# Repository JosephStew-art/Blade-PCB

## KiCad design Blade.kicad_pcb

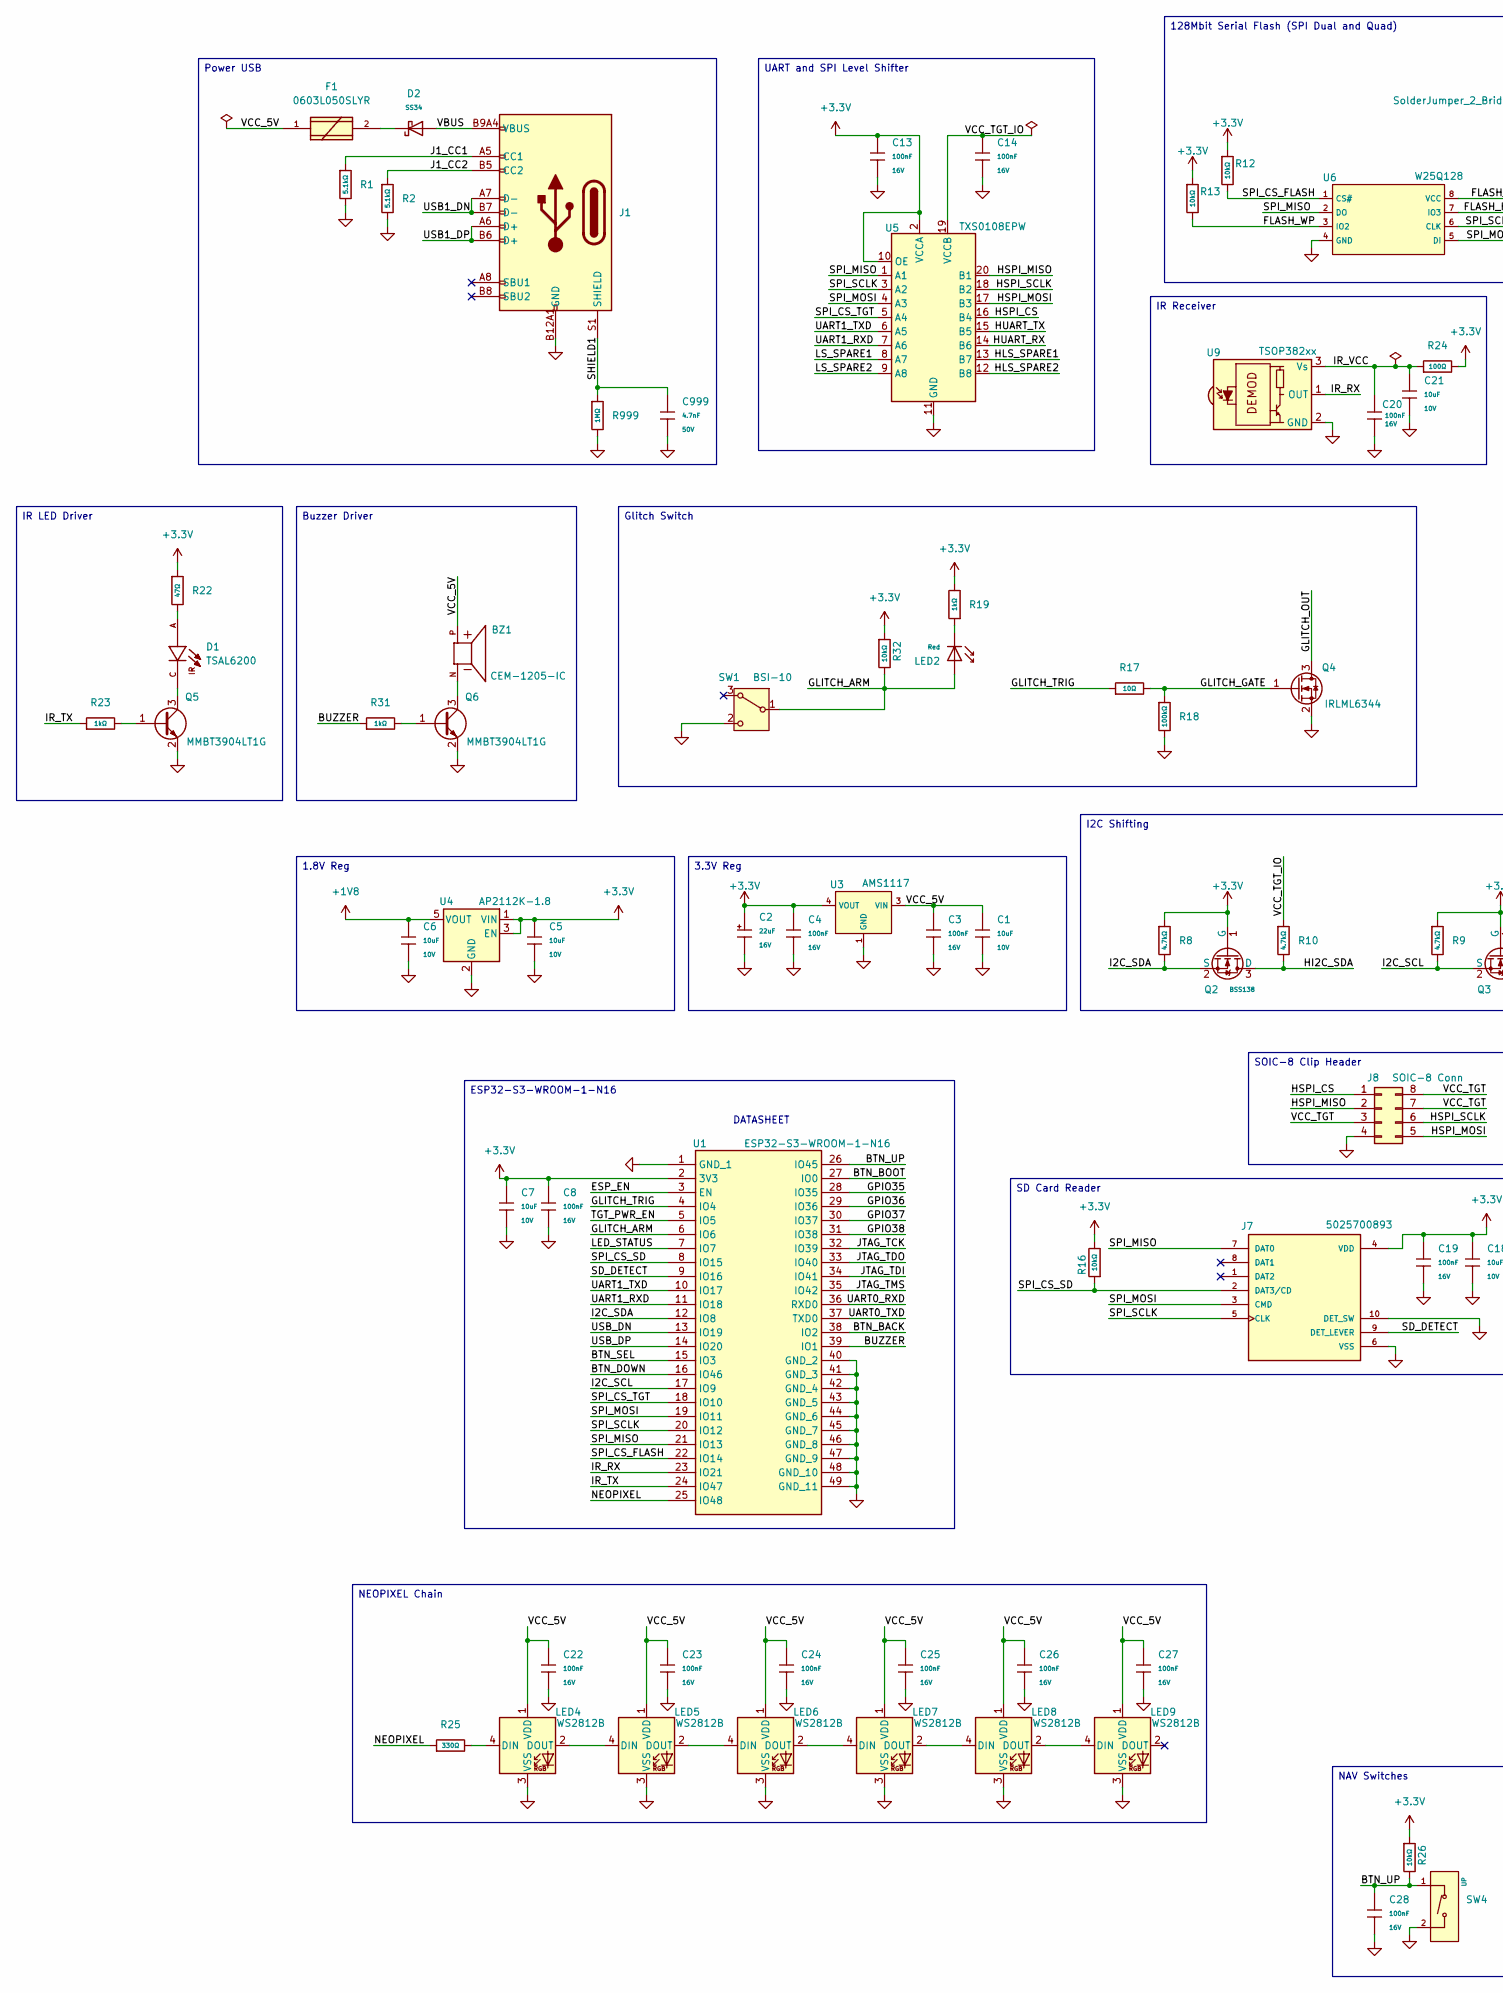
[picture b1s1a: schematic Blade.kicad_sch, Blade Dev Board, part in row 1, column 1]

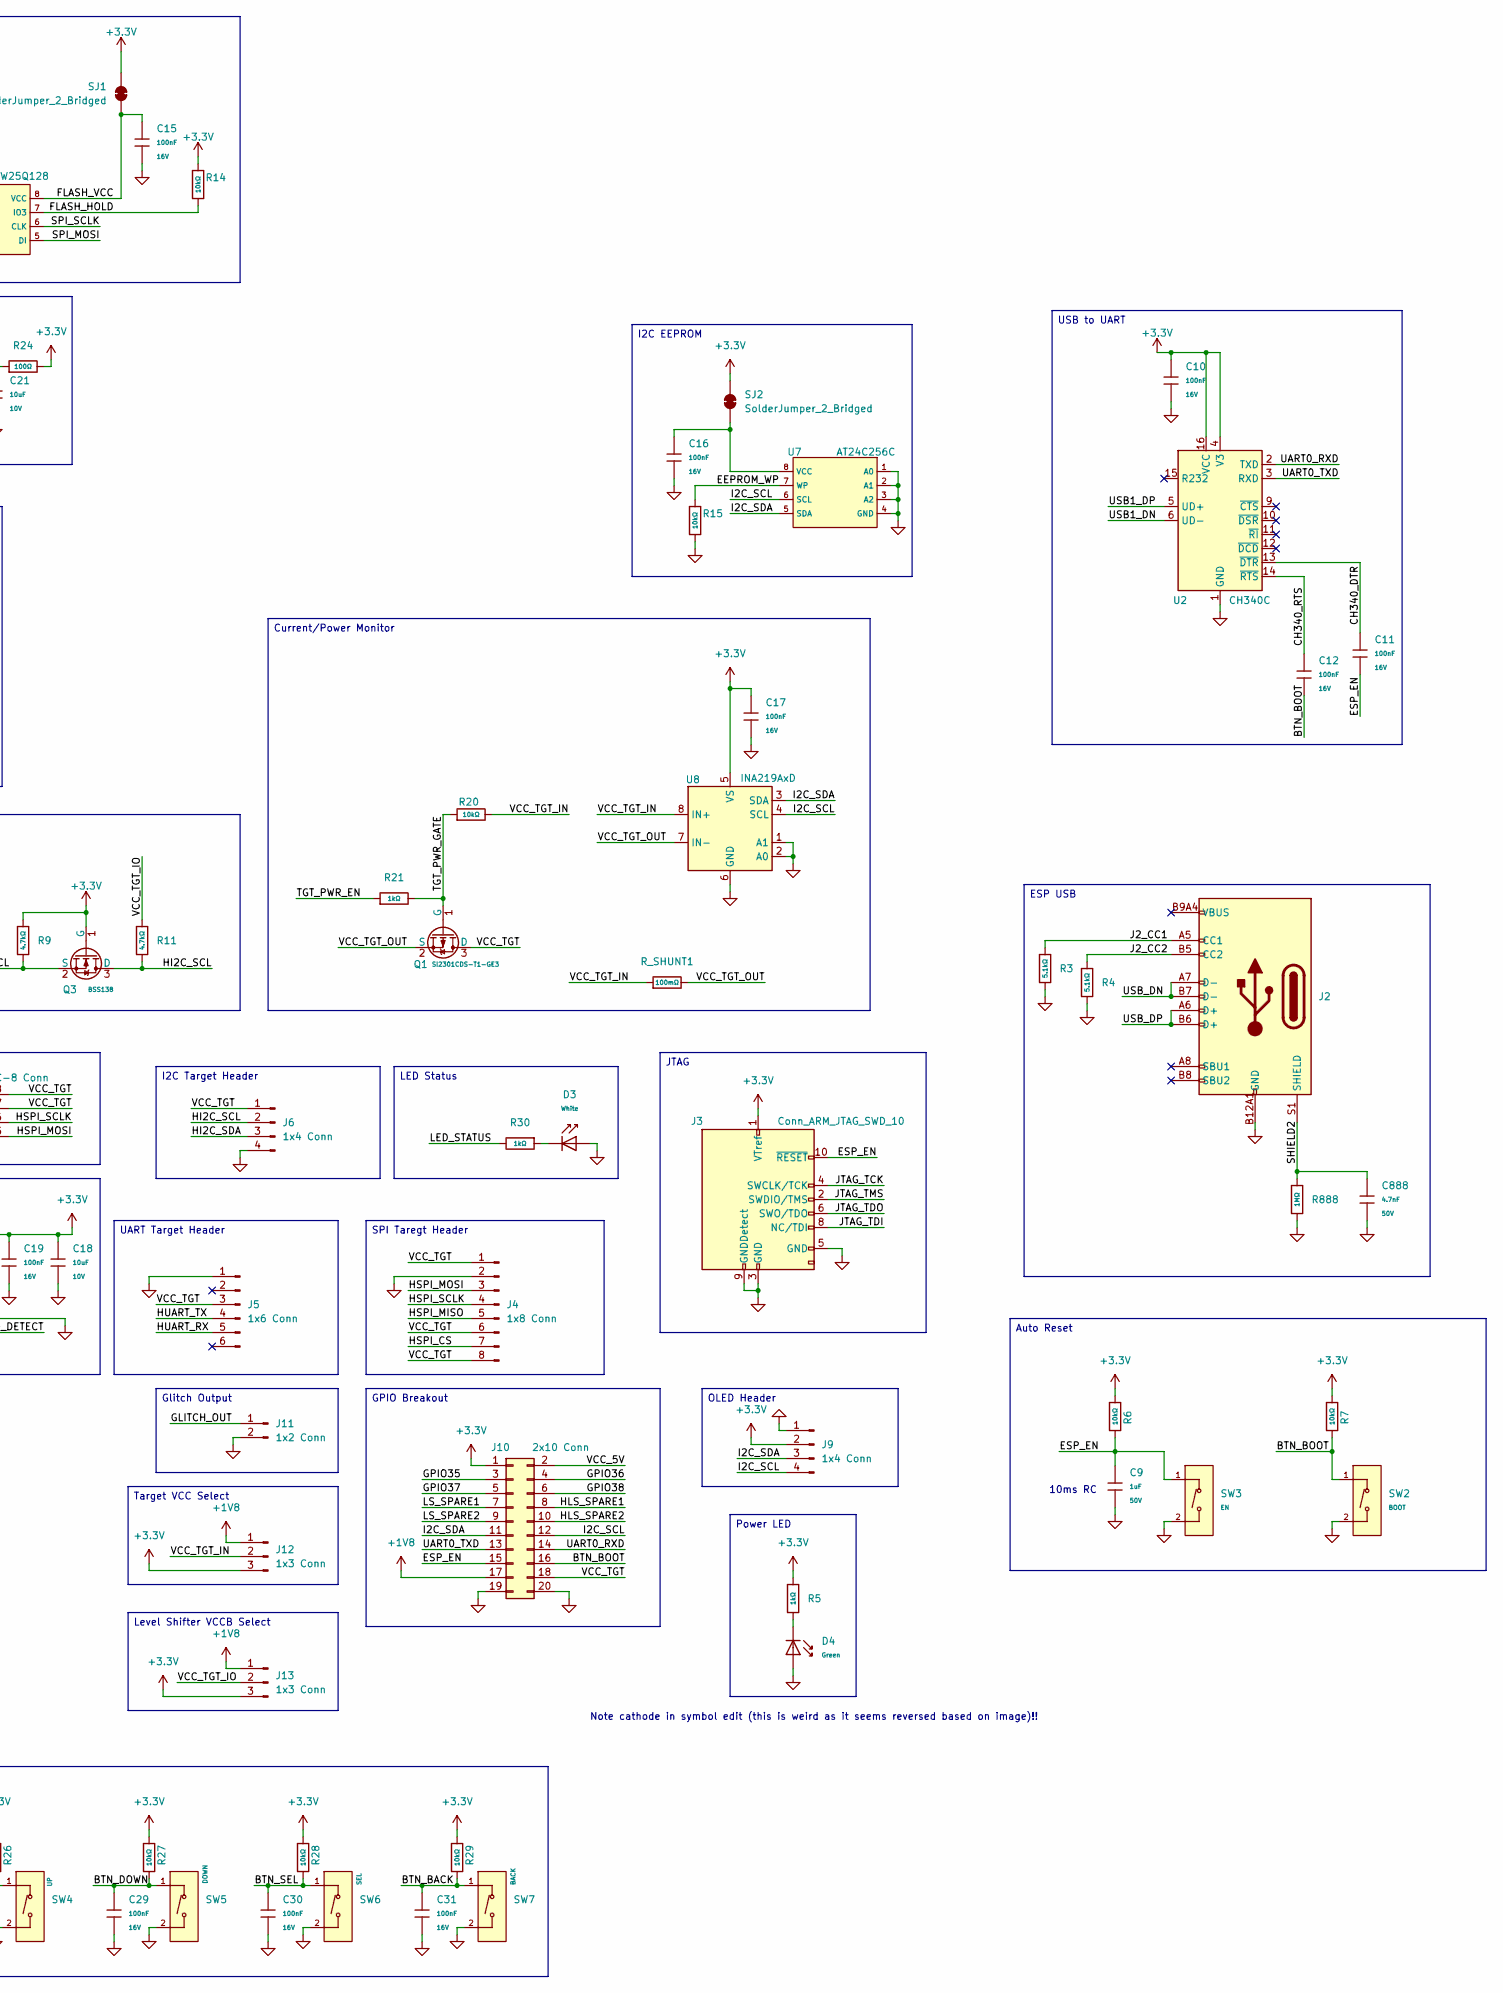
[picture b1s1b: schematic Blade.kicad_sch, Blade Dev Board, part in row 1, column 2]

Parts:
BZ1: CEM-1205-IC; PARTREV 1.02; LCSC C3812310
C1, C5, C6, C7, C18, C21: 10uF; C_0603; Voltage Rated 10V; Tolerance ±10%; Part CL10A106KP8NNNC; LCSC C19702
C2: 22uF; C_CASE-A-3216-18(mm); Tolerance ±10%; Rated Voltage 16V; Part TAJA106K016RNJ; LCSC C11366
C3, C4, C8, C10, C11, C12, C13, C14, C15, C16, C17, C19, C20, C22, C23, C24, C25, C26, C27, C28, C29, C30, C31: 100nF; C_0402; Voltage Rated 16V; Tolerance ±10%; Part CL05B104KO5NNNC; LCSC C1525
C9: 1uF; C_0603; Voltage Rated 50V; Tolerance ±10%; Part CL10A105KB8NNNC; LCSC C15849
C888, C999: 4.7nF; C_0805; Voltage Rated 50V; Tolerance ±10%; Part 0805B472K500NT; LCSC C1744
D1: TSAL6200; PARTREV 2.4; LCSC C55528
D2: SS34; D_SMA; Forward Voltage (Vf@If) 550mV@3A; Reverse Voltage (Vr) 40V; Part SS34; LCSC C8678
D3: White; D_0603; Part KT-0603W; LCSC C2290
D4: Green; D_0805; Part KT-0805G; LCSC C2297
F1: 0603L050SLYR; 6V05APTC; Mouser_Part_Number 576-0603L050SLYR
J1, J2: Connector, USB-TYPE-C-16P; TYPE-C-SMD_HX-TYPE-C-16PIN; LCSC C2927039
J3: Conn_ARM_JTAG_SWD_10; Tag-Connect_TC2050-IDC-FP_2x05_P1.27mm_Vertical
J4: 1x8 Conn; PinHeader_1x08_P2.54mm_Vertical
J5: 1x6 Conn; PinHeader_1x06_P2.54mm_Vertical
J6, J9: 1x4 Conn; PinHeader_1x04_P2.54mm_Vertical
J7: 5025700893; MOLEX_5025700893
J8: SOIC-8 Conn; PinHeader_2x04_P2.54mm_Vertical_Counter_Clockwise
J10: 2x10 Conn; PinHeader_2x10_P2.54mm_Vertical
J11: 1x2 Conn; PinHeader_1x02_P2.54mm_Vertical
J12, J13: 1x3 Conn; PinHeader_1x03_P2.54mm_Vertical
LED2: Red; D_0603; Part KT-0603R; LCSC C2286
LED4, LED5, LED6, LED7, LED8, LED9: WS2812B; LED_WS2812B_PLCC4_5.0x5.0mm_P3.2mm
Q1: SI2301CDS-T1-GE3; Q_SOT-23; Part SI2301CDS-T1-GE3; LCSC C10487
Q2, Q3: BSS138; Q_SOT-23; Part BSS138; LCSC C82045
Q4: IRLML6344; SOT-23; LCSC C5364313
Q5, Q6: MMBT3904LT1G; SOT-23; LCSC C81464
R1, R2, R3, R4: 5.1kΩ; R_0805; Overload Voltage (Max) 150V; Tolerance ±1%; Part 0805W8F5101T5E; LCSC C27834
R5, R19, R21, R23, R30, R31: 1kΩ; R_0805; Overload Voltage (Max) 150V; Tolerance ±1%; Part 0805W8F1001T5E; LCSC C17513
R6, R7, R12, R13, R14, R15, R16, R20, R26, R27, R28, R29, R32: 10kΩ; R_0805; Overload Voltage (Max) 150V; Tolerance ±1%; Part 0805W8F1002T5E; LCSC C17414
R8, R9, R10, R11: 4.7kΩ; R_0805; Overload Voltage (Max) 150V; Tolerance ±1%; Part 0805W8F4701T5E; LCSC C17673
R17: 10Ω; R_0805; Overload Voltage (Max) 150V; Tolerance ±1%; Part 0805W8F100JT5E; LCSC C17415
R18: 100kΩ; R_0805; Overload Voltage (Max) 150V; Tolerance ±1%; Part 0805W8F1003T5E; LCSC C149504
R22: 47Ω; R_0805; Overload Voltage (Max) 150V; Tolerance ±1%; Part 0805W8F470JT5E; LCSC C17714
R24: 100Ω; R_0805; Overload Voltage (Max) 150V; Tolerance ±1%; Part 0805W8F1000T5E; LCSC C17408
R25: 330Ω; R_0805; Overload Voltage (Max) 150V; Tolerance ±1%; Part 0805W8F3300T5E; LCSC C17630
R888, R999: 1MΩ; R_0805; Overload Voltage (Max) 150V; Tolerance ±1%; Part 0805W8F1004T5E; LCSC C17514
R_SHUNT1: 100mΩ; R_2512_6332Metric; Overload Voltage (Max) 200V; Tolerance ±1%; Part 1206W4F100LT5E; LCSC C23067426
SJ1, SJ2: SolderJumper_2_Bridged; SolderJumper-2_P1.3mm_Bridged_RoundedPad1.0x1.5mm
SW1: BSI-10; SW_Slide-03_Wuerth-WS-SLTV_10x2.5x6.4_P2.54mm; LCSC C2985934
SW2: BOOT; SW_TS-1088-AR02016; Voltage Rating (Dc) 12V; Part TS-1088-AR02016; LCSC C720477
SW3: EN; SW_TS-1088-AR02016; Voltage Rating (Dc) 12V; Part TS-1088-AR02016; LCSC C720477
SW4: UP; SW_TS-1088-AR02016; Voltage Rating (Dc) 12V; Part TS-1088-AR02016; LCSC C720477
SW5: DOWN; SW_TS-1088-AR02016; Voltage Rating (Dc) 12V; Part TS-1088-AR02016; LCSC C720477
SW6: SEL; SW_TS-1088-AR02016; Voltage Rating (Dc) 12V; Part TS-1088-AR02016; LCSC C720477
SW7: BACK; SW_TS-1088-AR02016; Voltage Rating (Dc) 12V; Part TS-1088-AR02016; LCSC C720477
U1: ESP32-S3-WROOM-1-N16; ESP32S3WROOM1N16; Mouser Part Number 356-ESP32S3WROOM1N16
U2: CH340C; SOIC-16_3.9x9.9mm_P1.27mm; LCSC C84681
U3: AMS1117; SOT-223-3_L6.5-W3.4-P2.30-LS7.0-BR; Output Voltage 3.3V; Dropout Voltage 1.3V@(800mA); Part AMS1117-3.3; LCSC C6186
U4: AP2112K-1.8; SOT-23-5; LCSC C176944
U5: TXS0108EPW; TSSOP-20_4.4x6.5mm_P0.65mm; LCSC C17206
U6: W25Q128; SOIC-8_L5.3-W5.3-P1.27-LS8.0-BL; Part W25Q128JVSIQ; LCSC C97521
U7: AT24C256C; SOIC-8_L4.9-W3.9-P1.27-LS6.0-BL; Supply Voltage 1.7V~5.5V; Part AT24C256C-SSHL-T; LCSC C6482
U8: INA219AxD; SOIC-8_3.9x4.9mm_P1.27mm; LCSC C138706
U9: TSOP382xx; Vishay_MINICAST-3Pin; LCSC C141632

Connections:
+1V8: C6.1, J10.17, J12.1, J13.1, U4.5 (VOUT)
+3.3V: C2.1, C4.1, C5.1, C7.1, C8.1, C10.1, C13.1, C17.1, C18.1, C19.1, J3.1 (VTref), J7.4 (VDD), J9.2, J10.1, J12.3, J13.3, Q2.1 (G), Q3.1 (G), R5.1, R6.1, R7.1, R8.1, R9.1, R12.1, R13.1, R14.1, R16.2, R19.2, R22.1, R24.2, R26.1, R27.1, R28.1, R29.1, R32.1, SJ1.2 (B), SJ2.2 (B), U1.2 (3V3), U2.4 (V3), U2.16 (VCC), U3.2 (VOUT), U3.4 (VOUT), U4.1 (VIN), U4.3 (EN), U5.2 (VCCA), U5.10 (OE), U8.5 (VS)
/BTN_BACK: C31.1, R29.2, SW7.1 (A), U1.38 (IO2)
/BTN_BOOT: C12.2, J10.16, R7.2, SW2.1 (A), U1.27 (IO0)
/BTN_DOWN: C29.1, R27.2, SW5.1 (A), U1.16 (IO46)
/BTN_SEL: C30.1, R28.2, SW6.1 (A), U1.15 (IO3)
/BTN_UP: C28.1, R26.2, SW4.1 (A), U1.26 (IO45)
/BUZZER: R31.1, U1.39 (IO1)
/CH340_DTR: C11.1, U2.13 (~DTR)
/CH340_RTS: C12.1, U2.14 (~RTS)
/EEPROM_WP: R15.1, U7.7 (WP)
/ESP_EN: C9.1, C11.2, J3.10 (~RESET), J10.15, R6.2, SW3.1 (A), U1.3 (EN)
/FLASH_HOLD: R14.2, U6.7 (IO3)
/FLASH_VCC: C15.1, SJ1.1 (A), U6.8 (VCC)
/FLASH_WP: R13.2, U6.3 (IO2)
/GLITCH_ARM: LED2.2, R32.2, SW1.1 (B), U1.6 (IO6)
/GLITCH_GATE: Q4.1 (G), R17.2, R18.1
/GLITCH_OUT: J11.1, Q4.3 (D)
/GLITCH_TRIG: R17.1, U1.4 (IO4)
/GPIO35: J10.3, U1.28 (IO35)
/GPIO36: J10.4, U1.29 (IO36)
/GPIO37: J10.5, U1.30 (IO37)
/GPIO38: J10.6, U1.31 (IO38)
/HI2C_SCL: J6.2, Q3.3 (D), R11.2
/HI2C_SDA: J6.3, Q2.3 (D), R10.2
/HLS_SPARE1: J10.8, U5.13 (B7)
/HLS_SPARE2: J10.10, U5.12 (B8)
/HSPI_CS: J4.7, J8.1, U5.16 (B4)
/HSPI_MISO: J4.5, J8.2, U5.20 (B1)
/HSPI_MOSI: J4.3, J8.5, U5.17 (B3)
/HSPI_SCLK: J4.4, J8.6, U5.18 (B2)
/HUART_RX: J5.5, U5.14 (B6)
/HUART_TX: J5.4, U5.15 (B5)
/I2C_SCL: J9.4, J10.12, Q3.2 (S), R9.2, U1.17 (IO9), U7.6 (SCL), U8.4 (SCL)
/I2C_SDA: J9.3, J10.11, Q2.2 (S), R8.2, U1.12 (IO8), U7.5 (SDA), U8.3 (SDA)
/IR_RX: U1.23 (IO21), U9.1 (OUT)
/IR_TX: R23.1, U1.24 (IO47)
/IR_VCC: C20.1, C21.1, R24.1, U9.3 (Vs)
/J1_CC1: J1.A5 (CC1), R1.1
/J1_CC2: J1.B5 (CC2), R2.1
/J2_CC1: J2.A5 (CC1), R3.1
/J2_CC2: J2.B5 (CC2), R4.1
/JTAG_TCK: J3.4 (SWCLK/TCK), U1.32 (IO39)
/JTAG_TDI: J3.8 (NC/TDI), U1.34 (IO41)
/JTAG_TDO: J3.6 (SWO/TDO), U1.33 (IO40)
/JTAG_TMS: J3.2 (SWDIO/TMS), U1.35 (IO42)
/LED_STATUS: R30.2, U1.7 (IO7)
/LS_SPARE1: J10.7, U5.8 (A7)
/LS_SPARE2: J10.9, U5.9 (A8)
/NEOPIXEL: R25.1, U1.25 (IO48)
/SD_DETECT: J7.9 (DET_LEVER), U1.9 (IO16)
/SHIELD1: C999.1, J1.S1 (SHIELD), R999.1
/SHIELD2: C888.1, J2.S1 (SHIELD), R888.1
/SPI_CS_FLASH: R12.2, U1.22 (IO14), U6.1 (CS#)
/SPI_CS_SD: J7.2 (DAT3/CD), R16.1, U1.8 (IO15)
/SPI_CS_TGT: U1.18 (IO10), U5.5 (A4)
/SPI_MISO: J7.7 (DAT0), U1.21 (IO13), U5.1 (A1), U6.2 (DO)
/SPI_MOSI: J7.3 (CMD), U1.19 (IO11), U5.4 (A3), U6.5 (DI)
/SPI_SCLK: J7.5 (CLK), U1.20 (IO12), U5.3 (A2), U6.6 (CLK)
/TGT_PWR_EN: R21.1, U1.5 (IO5)
/TGT_PWR_GATE: Q1.1 (G), R20.1, R21.2
/UART0_RXD: J10.14, U1.36 (RXD0), U2.2 (TXD)
/UART0_TXD: J10.13, U1.37 (TXD0), U2.3 (RXD)
/UART1_RXD: U1.11 (IO18), U5.7 (A6)
/UART1_TXD: U1.10 (IO17), U5.6 (A5)
/USB1_DN: J1.A7 (D-), J1.B7 (D-), U2.6 (UD-)
/USB1_DP: J1.A6 (D+), J1.B6 (D+), U2.5 (UD+)
/USB_DN: J2.A7 (D-), J2.B7 (D-), U1.13 (IO19)
/USB_DP: J2.A6 (D+), J2.B6 (D+), U1.14 (IO20)
/VBUS: D2.2, J1.A9B4 (VBUS), J1.B9A4 (VBUS)
/VCC_5V: BZ1.P, C1.1, C3.1, C22.1, C23.1, C24.1, C25.1, C26.1, C27.1, F1.1, J10.2, LED4.1 (VDD), LED5.1 (VDD), LED6.1 (VDD), LED7.1 (VDD), LED8.1 (VDD), LED9.1 (VDD), U3.3 (VIN)
/VCC_TGT: J4.1, J4.6, J4.8, J5.3, J6.1, J8.3, J8.7, J8.8, J10.18, Q1.3 (D)
/VCC_TGT_IN: J12.2, R20.2, R_SHUNT1.1, U8.8 (IN+)
/VCC_TGT_IO: C14.1, J13.2, R10.1, R11.1, U5.19 (VCCB)
/VCC_TGT_OUT: Q1.2 (S), R_SHUNT1.2, U8.7 (IN-)
GND: C1.2, C2.2, C3.2, C4.2, C5.2, C6.2, C7.2, C8.2, C9.2, C10.2, C13.2, C14.2, C15.2, C16.2, C17.2, C18.2, C19.2, C20.2, C21.2, C22.2, C23.2, C24.2, C25.2, C26.2, C27.2, C28.2, C29.2, C30.2, C31.2, C888.2, C999.2, D3.2, D4.2, J1.A12B1 (GND), J1.B12A1 (GND), J2.A12B1 (GND), J2.B12A1 (GND), J3.3 (GND), J3.5 (GND), J3.9 (GNDDetect), J4.2, J5.1, J6.4, J7.6 (VSS), J7.10 (DET_SW), J8.4, J9.1, J10.19, J10.20, J11.2, LED4.3 (VSS), LED5.3 (VSS), LED6.3 (VSS), LED7.3 (VSS), LED8.3 (VSS), LED9.3 (VSS), Q4.2 (S), Q5.2 (E), Q6.2 (E), R1.2, R2.2, R3.2, R4.2, R15.2, R18.2, R888.2, R999.2, SW1.2 (C), SW2.2 (B), SW3.2 (B), SW4.2 (B), SW5.2 (B), SW6.2 (B), SW7.2 (B), U1.1 (GND_1), U1.40 (GND_2), U1.41 (GND_3), U1.42 (GND_4), U1.43 (GND_5), U1.44 (GND_6), U1.45 (GND_7), U1.46 (GND_8), U1.47 (GND_9), U1.48 (GND_10), U1.49 (GND_11), U2.1 (GND), U3.1 (GND), U4.2 (GND), U5.11 (GND), U6.4 (GND), U7.1 (A0), U7.2 (A1), U7.3 (A2), U7.4 (GND), U8.1 (A1), U8.2 (A0), U8.6 (GND), U9.2 (GND)
unnamed: D1.A, R22.2
unnamed: D2.1, F1.2
unnamed: D3.1, R30.1
unnamed: D4.1, R5.2
unnamed: LED2.1, R19.1
unnamed: LED4.4 (DIN), R25.2
unnamed: LED4.2 (DOUT), LED5.4 (DIN)
unnamed: LED5.2 (DOUT), LED6.4 (DIN)
unnamed: LED6.2 (DOUT), LED7.4 (DIN)
unnamed: LED7.2 (DOUT), LED8.4 (DIN)
unnamed: LED8.2 (DOUT), LED9.4 (DIN)
unnamed: Q5.1 (B), R23.2
unnamed: D1.C, Q5.3 (C)
unnamed: Q6.1 (B), R31.2
unnamed: BZ1.N, Q6.3 (C)
unnamed: C16.1, SJ2.1 (A), U7.8 (VCC)

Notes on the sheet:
Note cathode in symbol edit (this is weird as it seems reversed based on image)!!
DATASHEET
10ms RC
Power LED
LED Status
Buzzer Driver
NEOPIXEL Chain
I2C Shifting
ESP USB
I2C Target Header
Glitch Output
UART Target Header
IR LED Driver
Current/Power Monitor
IR Receiver
Glitch Switch
NAV Switches
1.8V Reg
Auto Reset
SPI Taregt Header
ESP32-S3-WROOM-1-N16
OLED Header
JTAG
Power USB
SOIC-8 Clip Header
SD Card Reader
Level Shifter VCCB Select
UART and SPI Level Shifter
USB to UART
Target VCC Select
3.3V Reg
I2C EEPROM
GPIO Breakout
128Mbit Serial Flash (SPI Dual and Quad)

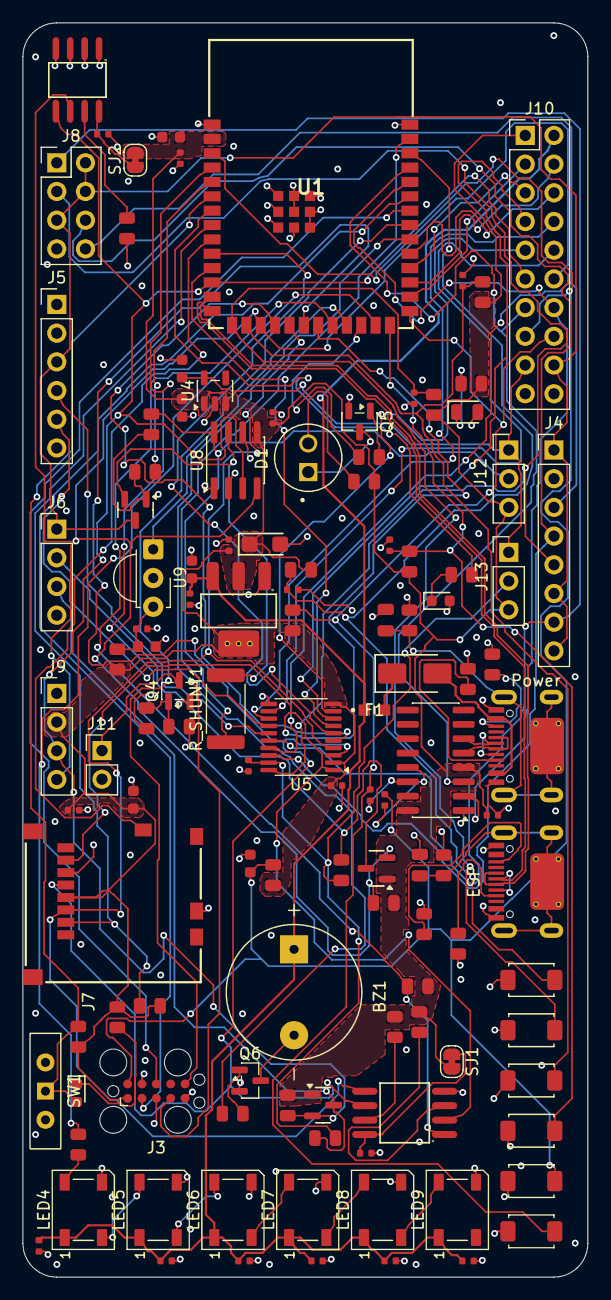
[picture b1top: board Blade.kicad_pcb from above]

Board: 4 copper layers, 50.0 x 111.0 mm, 118 parts (0 on the bottom side), 92 nets.

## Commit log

2026-03-08 Initial Blade-PCB import
2026-03-15 Add redirection page for import guide
2026-03-15 Add schematic section to README with embedded PDF
2026-03-15 Replace PDF schematic with PNG image in README and remove PDF file
2026-03-15 Add Blade image and update README with board section
    - Added Blade.png image to the repository.
    - Updated README.md to include a new section for the board with the Blade image.
